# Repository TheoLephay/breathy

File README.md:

# Breathy

Work in progress.

An IOT esp32-based, battery powered, air quality monitor.

Since this is the least original project but I still needed one, I decided to make the li-ion charger myself as a challenge with discreet components.

Hardware design sheets available under `hardware/breathy/` folder. SPICE sim under `hardware/spice_sims/`.

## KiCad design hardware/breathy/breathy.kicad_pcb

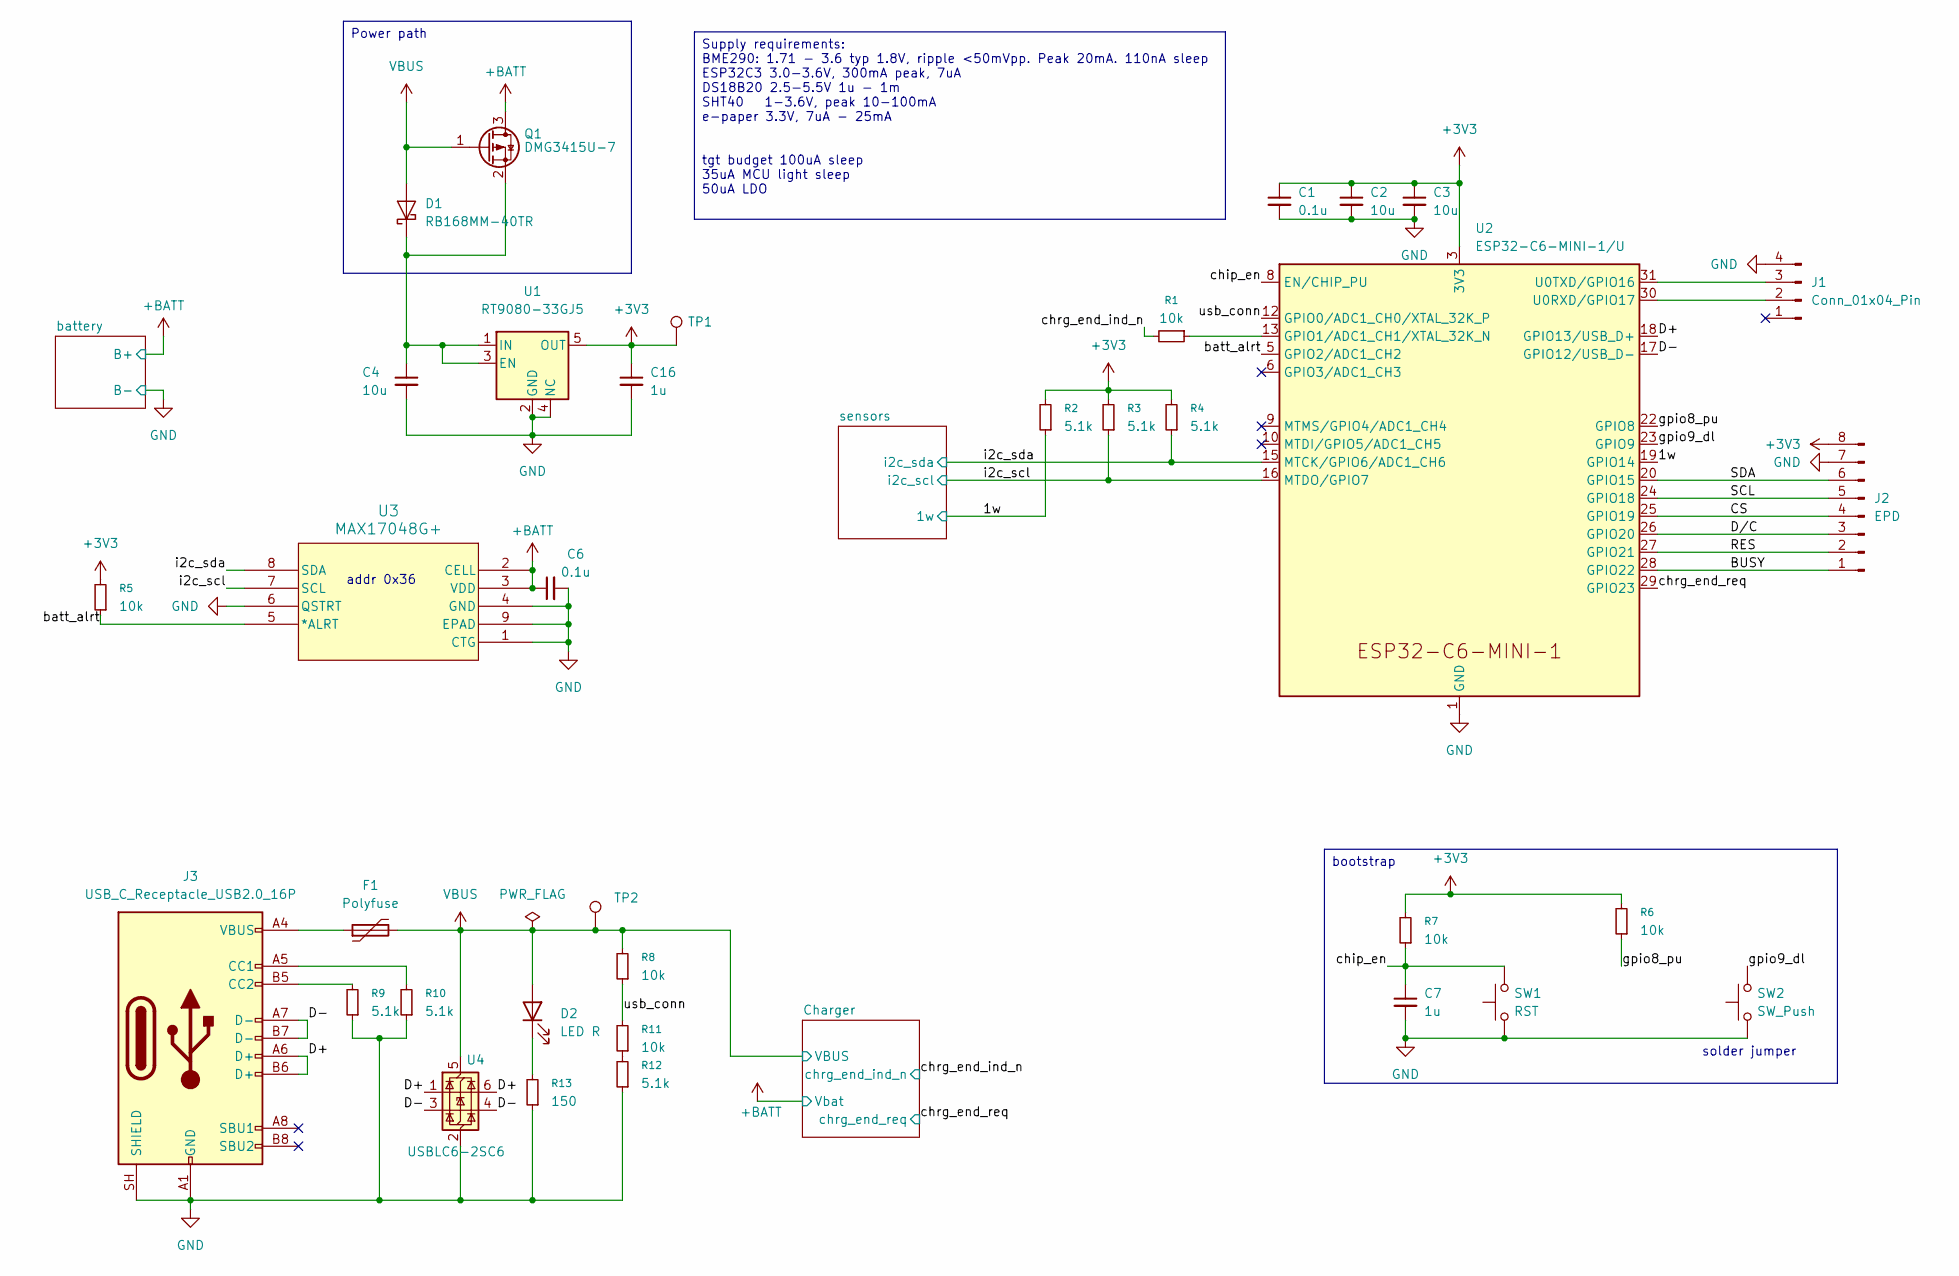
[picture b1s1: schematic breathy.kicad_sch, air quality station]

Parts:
C1, C6: 0.1u; C_0805_2012Metric
C2, C3, C4: 10u; C_1206_3216Metric
C7, C16: 1u; C_1206_3216Metric
D1: RB168MM-40TR; Nexperia_CFP3_SOD-123W
D2: LED R; LED_1206_3216Metric
F1: Polyfuse; C_1206_3216Metric
J1: Conn_01x04_Pin; PinHeader_1x04_P2.54mm_Vertical
J2: EPD; PinHeader_1x08_P2.54mm_Horizontal
J3: USB_C_Receptacle_USB2.0_16P; USB_C_Receptacle_GCT_USB4105-xx-A_16P_TopMnt_Horizontal
Q1: DMG3415U-7; SOT-23
R1, R5, R6, R7, R8, R11: 10k; R_0805_2012Metric
R2, R3, R4, R9, R10, R12: 5.1k; R_0805_2012Metric
R13: 150; R_0805_2012Metric
SW1: RST; SW_Push_1P1T_NO_CK_KSC9xxG
SW2: SW_Push; SolderJumper-2_P1.3mm_Open_TrianglePad1.0x1.5mm
TP1, TP2: TestPoint; TestPoint_Pad_D1.5mm
U1: RT9080-33GJ5; SOT-23-5
U2: ESP32-C6-MINI-1/U; ESP32-C6-MINI-1
U3: MAX17048G+; 21-0168_T822&plus_3_MXM-M
U4: USBLC6-2SC6; SOT-23-6

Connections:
+3V3: C1.1, C2.1, C3.1, C16.1, J2.8, R2.2, R3.2, R4.2, R5.2, R6.2, R7.2, TP1.1 (1_1), U1.5 (OUT), U2.3 (3V3); also elsewhere on the board
+BATT: C6.1, Q1.3 (D), U3.2 (CELL), U3.3 (VDD); also elsewhere on the board
/1w: R2.1, U2.19 (GPIO14); also elsewhere on the board
/BUSY: J2.1, U2.28 (GPIO22)
/CS: J2.4, U2.25 (GPIO19)
/D+: J3.A6 (D+), J3.B6 (D+), U2.18 (GPIO13/USB_D+), U4.1 (I/O1), U4.6 (I/O1)
/D-: J3.A7 (D-), J3.B7 (D-), U2.17 (GPIO12/USB_D-), U4.3 (I/O2), U4.4 (I/O2)
/D/C: J2.3, U2.26 (GPIO20)
/RES: J2.2, U2.27 (GPIO21)
/SCL: J2.5, U2.24 (GPIO18)
/SDA: J2.6, U2.20 (GPIO15)
/batt_alrt: R5.1, U2.5 (GPIO2/ADC1_CH2), U3.5 (*ALRT)
/chip_en: C7.1, R7.1, SW1.2, U2.8 (EN/CHIP_PU)
/chrg_end_ind_n: R1.2; also elsewhere on the board
/chrg_end_req: U2.29 (GPIO23); also elsewhere on the board
/gpio8_pu: R6.1, U2.22 (GPIO8)
/gpio9_dl: SW2.2, U2.23 (GPIO9)
/i2c_scl: R3.1, U2.16 (MTDO/GPIO7), U3.7 (SCL); also elsewhere on the board
/i2c_sda: R4.1, U2.15 (MTCK/GPIO6/ADC1_CH6), U3.8 (SDA); also elsewhere on the board
/usb_conn: R8.1, R11.2, U2.12 (GPIO0/ADC1_CH0/XTAL_32K_P)
GND: C1.2, C2.2, C3.2, C4.2, C6.2, C7.2, C16.2, J1.4, J2.7, J3.A1 (GND), J3.A12 (GND), J3.B1 (GND), J3.B12 (GND), J3.SH (SHIELD), R9.1, R10.1, R12.1, R13.1, SW1.1, SW2.1, U1.2 (GND), U1.4 (NC), U2.1 (GND), U2.2 (GND), U2.11 (GND), U2.14 (GND), U2.36 (GND), U2.37 (GND), U2.38 (GND), U2.39 (GND), U2.40 (GND), U2.41 (GND), U2.42 (GND), U2.43 (GND), U2.44 (GND), U2.45 (GND), U2.46 (GND), U2.47 (GND), U2.48 (GND), U2.49 (GND), U2.50 (GND), U2.51 (GND), U2.52 (GND), U2.53 (GND), U3.1 (CTG), U3.4 (GND), U3.6 (QSTRT), U3.9 (EPAD), U4.2 (GND); also elsewhere on the board
unnamed: C4.1, D1.1 (K), Q1.2 (S), U1.1 (IN), U1.3 (EN)
unnamed: D2.1 (K), R13.2
unnamed: F1.1, J3.A4 (VBUS), J3.A9 (VBUS), J3.B4 (VBUS), J3.B9 (VBUS)
unnamed: J1.2, U2.30 (U0RXD/GPIO17)
unnamed: J1.3, U2.31 (U0TXD/GPIO16)
unnamed: J3.A5 (CC1), R10.2
unnamed: J3.B5 (CC2), R9.2
unnamed: R11.1, R12.2
unnamed: R1.1, U2.13 (GPIO1/ADC1_CH1/XTAL_32K_N)
VBUS: D1.2 (A), D2.2 (A), F1.2, Q1.1 (G), R8.2, TP2.1 (1_1), U4.5 (VBUS); also elsewhere on the board

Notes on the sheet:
solder jumper
addr 0x36
Supply requirements: BME290: 1.71 - 3.6 typ 1.8V, ripple <50mVpp. Peak 20mA. 110nA sleep ESP32C3 3.0-3.6V, 300mA peak, 7uA DS18B20 2.5-5.5V 1u - 1m SHT40 1-3.6V, peak 10-100mA e-paper 3.3V, 7uA - 25mA tgt budget 100uA sleep 35uA MCU light sleep 50uA LDO
Power path
bootstrap

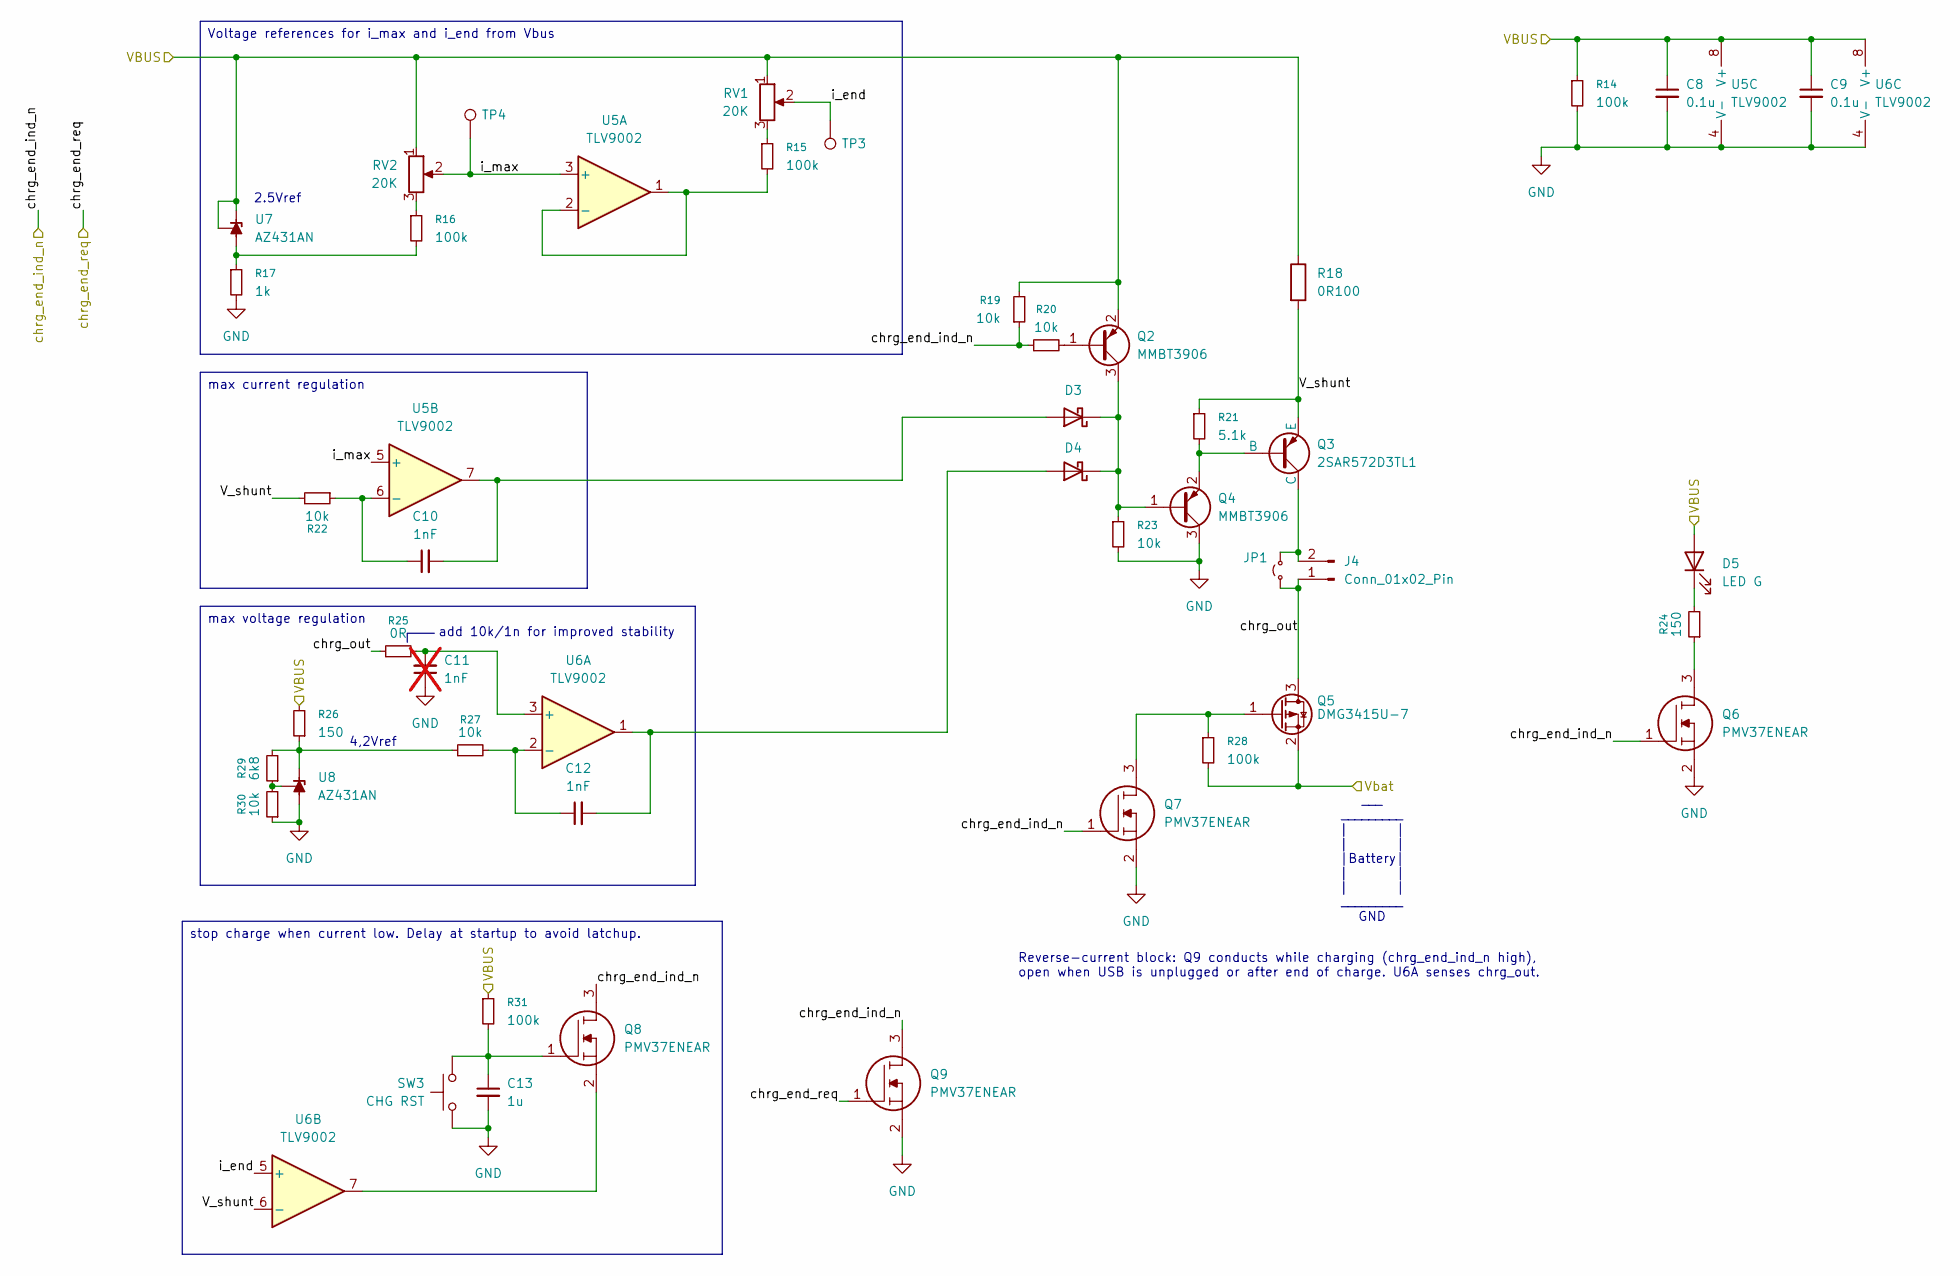
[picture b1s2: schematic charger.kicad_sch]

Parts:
C8, C9: 0.1u; C_0805_2012Metric
C10, C12: 1nF; C_0805_2012Metric
C11: 1nF; C_0805_2012Metric; not fitted
C13: 1u; C_1206_3216Metric
D3, D4: D_Schottky; D_SOD-323_HandSoldering
D5: LED G; LED_1206_3216Metric
J4: Conn_01x02_Pin; PinHeader_1x02_P2.54mm_Vertical
JP1: Jumper_2_Small_Open; SolderJumper-2_P1.3mm_Open_TrianglePad1.0x1.5mm
Q2, Q4: MMBT3906; SOT-23
Q3: 2SAR572D3TL1; TO-252-2
Q5: DMG3415U-7; SOT-23
Q6, Q7, Q8, Q9: PMV37ENEAR; SOT95P230X110-3N; Mouser Part Number 771-PMV37ENEAR
R14, R15, R16, R28, R31: 100k; R_1206_3216Metric
R17: 1k; R_1206_3216Metric
R18: 0R100; R_2010_5025Metric_Pad1.40x2.65mm_HandSolder
R19, R20, R22, R23, R27, R30: 10k; R_0805_2012Metric
R21: 5.1k; R_0805_2012Metric
R24, R26: 150; R_0805_2012Metric
R25: 0R; R_0805_2012Metric
R29: 6k8; R_0805_2012Metric
RV1, RV2: 20K; Potentiometer_Bourns_TC33X_Vertical
SW3: CHG RST; SW_Push_1P1T_NO_CK_KSC9xxG
TP3, TP4: TestPoint; TestPoint_Pad_D1.5mm
U5, U6: TLV9002; TSOT-23-8
U7, U8: AZ431AN; SOT-23

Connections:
+BATT: Q5.2 (S), R28.2; also elsewhere on the board
/Charger/V_shunt: Q3.3 (E), R18.2, R21.1, R22.2, U6.6 (-)
/Charger/chrg_out: J4.1, JP1.1 (A), Q5.3 (D), R25.1
/Charger/i_end: RV1.2, TP3.1 (1_1), U6.5 (+)
/Charger/i_max: RV2.2, TP4.1 (1_1), U5.3 (+), U5.5 (+)
/chrg_end_ind_n: Q6.1, Q7.1, Q8.3, Q9.3, R19.1, R20.1; also elsewhere on the board
/chrg_end_req: Q9.1; also elsewhere on the board
GND: C8.2, C9.2, C11.1, C13.2, Q4.3 (C), Q6.2, Q7.2, Q9.2, R14.2, R17.2, R23.2, R30.1, SW3.1, U5.4 (V-), U6.4 (V-), U8.3 (A); also elsewhere on the board
unnamed: C13.1, Q8.1, R31.2, SW3.2
unnamed: C10.2, D3.2 (A), U5.7
unnamed: D3.1 (K), D4.1 (K), Q2.3 (C), Q4.1 (B), R23.1
unnamed: C12.2, D4.2 (A), U6.1
unnamed: D5.1 (K), R24.2
unnamed: J4.2, JP1.2 (B), Q3.2 (C)
unnamed: Q2.1 (B), R20.2
unnamed: Q3.1 (B), Q4.2 (E), R21.2
unnamed: Q5.1 (G), Q7.3, R28.1
unnamed: Q6.3, R24.1
unnamed: Q8.2, U6.7
unnamed: R15.1, RV1.3
unnamed: R16.1, RV2.3
unnamed: R15.2, U5.1, U5.2 (-)
unnamed: C10.1, R22.1, U5.6 (-)
unnamed: C11.2, R25.2, U6.3 (+)
unnamed: C12.1, R27.2, U6.2 (-)
unnamed: R16.2, R17.1, U7.3 (A)
unnamed: R26.1, R27.1, R29.2, U8.2 (K)
unnamed: R29.1, R30.2, U8.1 (REF)
VBUS: C8.1, C9.1, D5.2 (A), Q2.2 (E), R14.1, R18.1, R19.2, R26.2, R31.1, RV1.1, RV2.1, U5.8 (V+), U6.8 (V+), U7.1 (REF), U7.2 (K); also elsewhere on the board

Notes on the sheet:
___ _________ | | | | |Battery| | | | | _________ GND
2.5Vref
Reverse-current block: Q9 conducts while charging (chrg_end_ind_n high), open when USB is unplugged or after end of charge. U6A senses chrg_out.
add 10k/1n for improved stability
4,2Vref
stop charge when current low. Delay at startup to avoid latchup.
Voltage references for i_max and i_end from Vbus
max current regulation
max voltage regulation

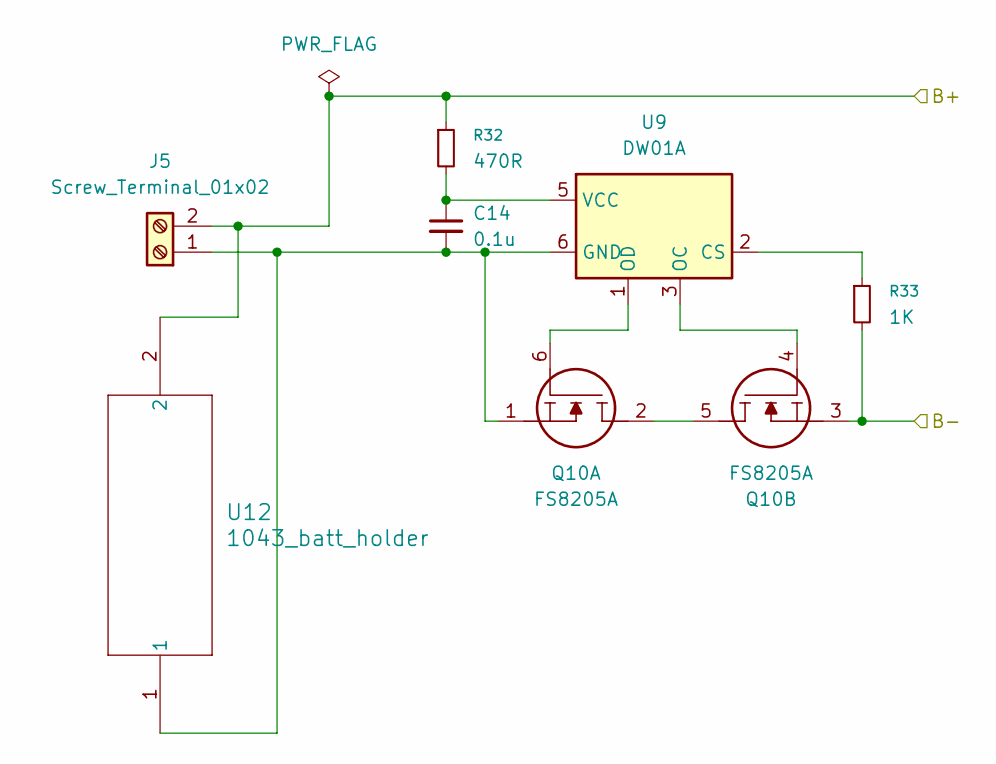
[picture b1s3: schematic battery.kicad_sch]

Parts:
C14: 0.1u; C_0805_2012Metric
J5: Screw_Terminal_01x02; TerminalBlock_MaiXu_MX126-5.0-02P_1x02_P5.00mm
Q10: FS8205A; SOT-23-6
R32: 470R; R_0805_2012Metric
R33: 1K; R_1206_3216Metric
U9: DW01A; SOT-23-6
U12: 1043_batt_holder; 1043_battery_holder_18650

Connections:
+BATT: J5.2, R32.1, U12.2; also elsewhere on the board
GND: Q10.3 (S2), R33.2; also elsewhere on the board
unnamed: C14.2, J5.1, Q10.1 (S1), U9.6 (GND), U12.1
unnamed: Q10.2 (D1), Q10.5 (D2)
unnamed: Q10.6 (G1), U9.1 (OD)
unnamed: Q10.4 (G2), U9.3 (OC)
unnamed: R33.1, U9.2 (CS)
unnamed: C14.1, R32.2, U9.5 (VCC)

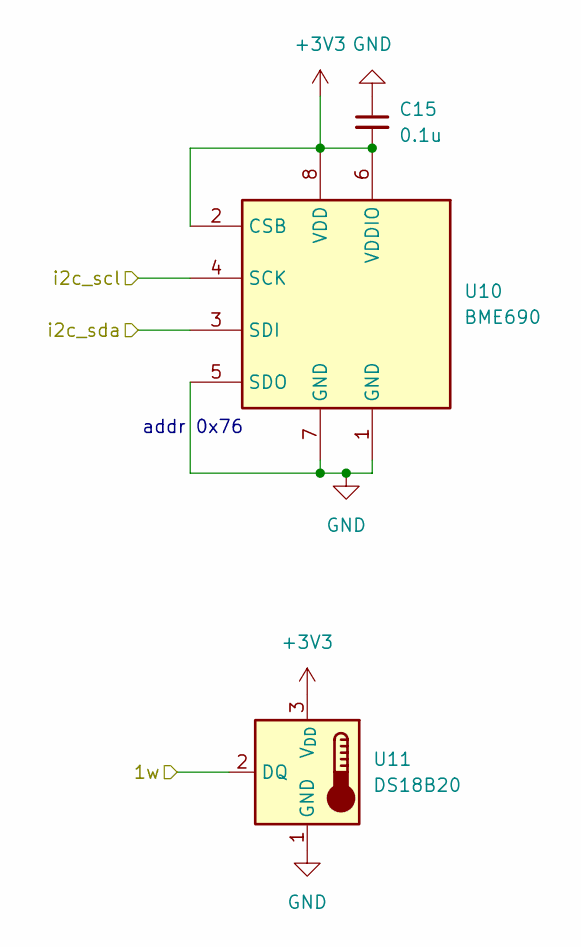
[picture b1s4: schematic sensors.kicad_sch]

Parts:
C15: 0.1u; C_0805_2012Metric
U10: BME690; Bosch_LGA-8_3x3mm_P0.8mm_ClockwisePinNumbering
U11: DS18B20; TO-92_Inline

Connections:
+3V3: C15.2, U10.2 (CSB), U10.6 (VDDIO), U10.8 (VDD), U11.3 (V_{DD}); also elsewhere on the board
/1w: U11.2 (DQ); also elsewhere on the board
/i2c_scl: U10.4 (SCK); also elsewhere on the board
/i2c_sda: U10.3 (SDI); also elsewhere on the board
GND: C15.1, U10.1 (GND), U10.5 (SDO), U10.7 (GND), U11.1 (GND); also elsewhere on the board

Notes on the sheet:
addr 0x76

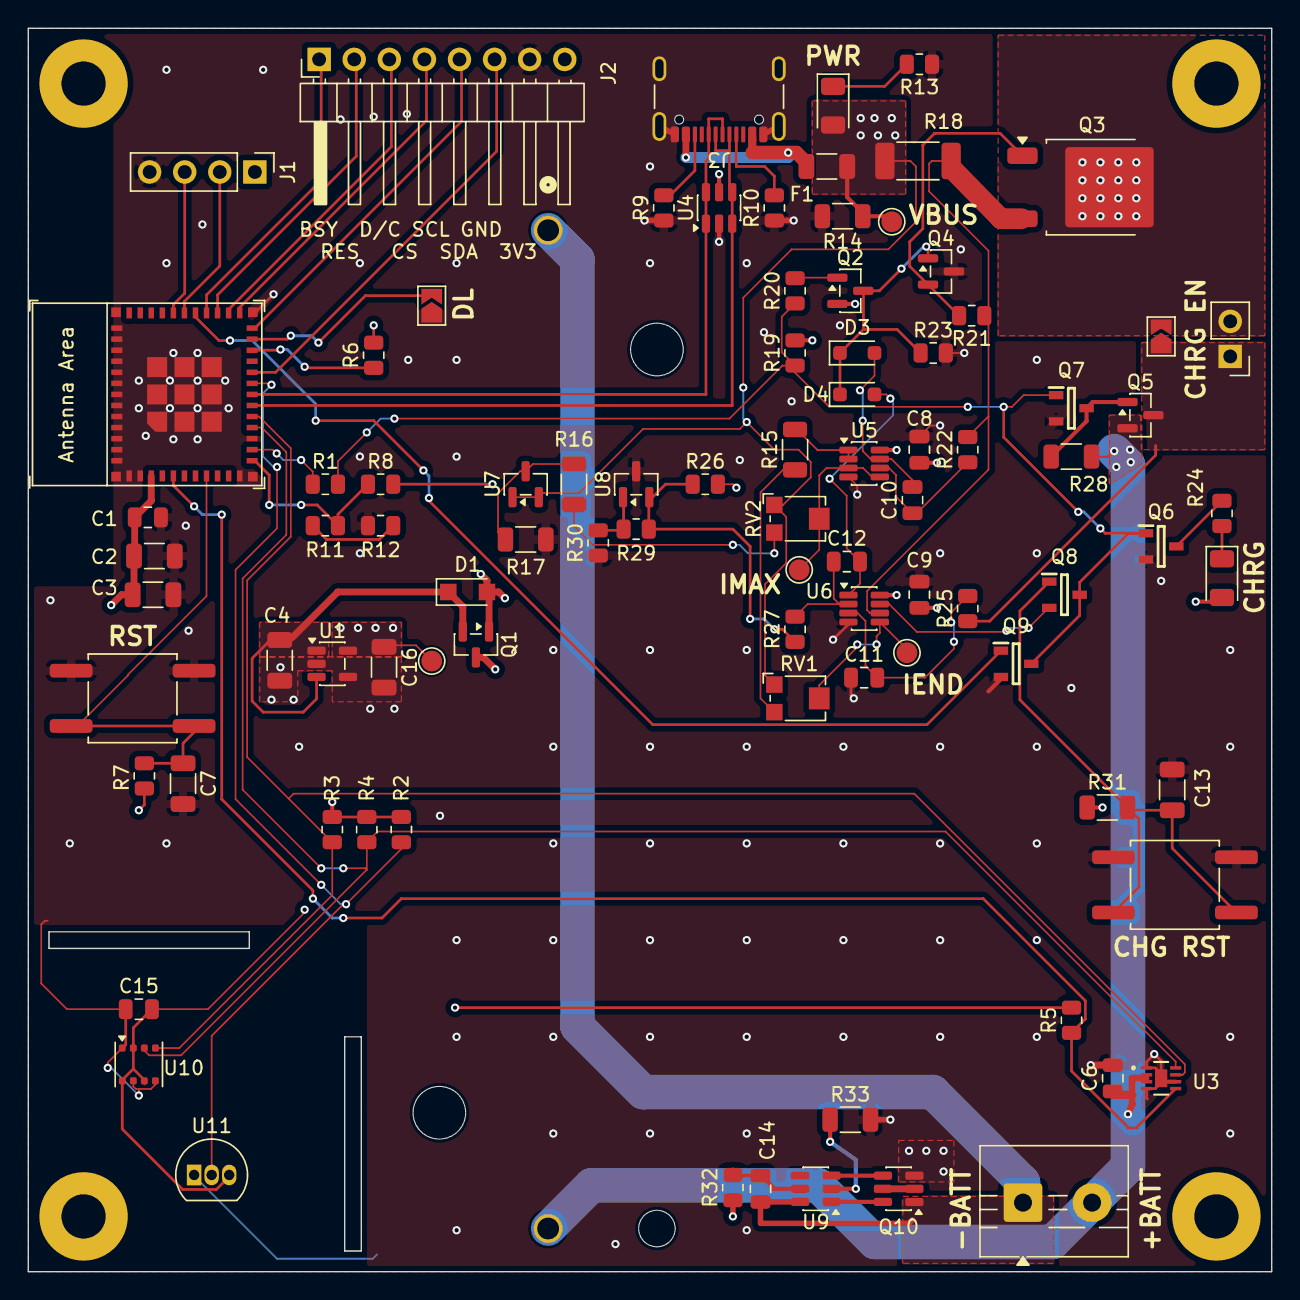
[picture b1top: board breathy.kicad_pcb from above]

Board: 4 copper layers, 90.0 x 90.0 mm, 95 parts (1 on the bottom side), 61 nets.

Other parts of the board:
H1, H2, H3, H4: MountingHole_3.2mm_M3_Pad
